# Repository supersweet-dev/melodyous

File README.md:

# melodyous

A qtpy shoe for converting MIDI messages to tape speed control voltage.
wip

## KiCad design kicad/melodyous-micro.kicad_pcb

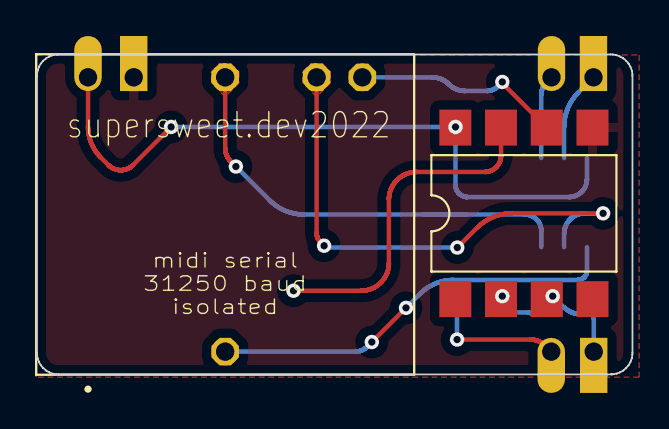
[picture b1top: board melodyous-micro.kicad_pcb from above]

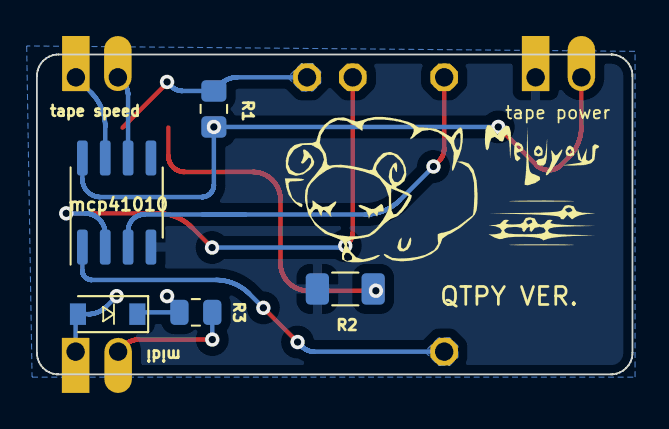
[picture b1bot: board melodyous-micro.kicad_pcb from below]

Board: 2 copper layers, 33.1 x 17.8 mm, 9 parts (6 on the bottom side), 12 nets.

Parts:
D1: swd; D_SOD-123
ISOLATOR1: 6N138; SMDIP-8_W9.53mm
J1: TRS; PinHeader_1x02_P1.27mm_Vertical
POT1: Tape Pot; PinHeader_1x02_P1.27mm_Vertical
R1: 10KOhm; R_0805_2012Metric_Pad1.20x1.40mm_HandSolder
R2: 470Ohm; R_1206_3216Metric_Pad1.30x1.75mm_HandSolder
R3: 220Ohm; R_0805_2012Metric
U1: qtpy
mcp41010: MCP41010; SOIC-8_3.9x4.9mm_P1.27mm

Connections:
+5V: ISOLATOR1.8 (VCC), R1.2, U1.14 (5V), mcp41010.8 (VDD)
GND: ISOLATOR1.5 (GND), R2.2, U1.13 (GND), mcp41010.4 (VSS)
unnamed: D1.1 (K), ISOLATOR1.2 (C1), R3.2
unnamed: D1.2 (A), ISOLATOR1.3 (C2), J1.C
unnamed: ISOLATOR1.6 (VO2), R1.1, U1.8 (RX)
unnamed: ISOLATOR1.7 (VO1), R2.1
unnamed: J1.A, R3.1
unnamed: POT1.SPEEDGND, mcp41010.7 (PB0)
unnamed: POT1.SPEEDW, mcp41010.6 (PW0)
unnamed: U1.4 (A3), mcp41010.1 (~CS)
unnamed: U1.9 (SCK), mcp41010.2 (SCK)
unnamed: U1.11 (MOSI), mcp41010.3 (SI)

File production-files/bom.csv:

Designator,Footprint,Quantity,Value,LCSC Part #
D1,D_SOD-123,1,swd,
ISOLATOR1,SMDIP-8_W9.53mm,1,6N138,
J1,PinHeader_1x02_P1.27mm_Vertical,1,TRS,
POT1,PinHeader_1x02_P1.27mm_Vertical,1,Tape Pot,
R1,R_0805_2012Metric_Pad1.20x1.40mm_HandSolder,1,10KOhm,
R2,R_1206_3216Metric_Pad1.30x1.75mm_HandSolder,1,470Ohm,
R3,R_0805_2012Metric,1,220Ohm,
U1,qtpy,1,qtpy,
mcp41010,SOIC-8_3.9x4.9mm_P1.27mm,1,MCP41010,

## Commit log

2022-11-15 init
2022-12-27 qtpy version
